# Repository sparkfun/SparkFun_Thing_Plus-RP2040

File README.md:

SparkFun Thing Plus RP2040
========================================

[*SparkFun Thing Plus RP2040 (DEV-17745)*](https://www.sparkfun.com/products/17745)

The SparkFun Thing Plus - RP2040 is a low-cost, high performance board with flexible digital interfaces featuring the Raspberry Pi Foundation's RP2040 microcontroller. Besides the Thing Plus or *Feather* footprint (with 18 GPIO pins), the board also includes an SD card slot, 16MB (128Mbit) flash memory, a JST single cell battery connector (with a charging circuit and fuel gauge sensor), an addressable WS2812 RGB LED, JTAG PTH pins, four (4-40 screw) mounting holes, and our signature Qwiic connector.

The RP2040 is supported with both C/C++ and MicroPython cross-platform development environments, including easy access to runtime debugging. It has UF2 boot and floating-point routines baked into the chip. While the chip has a large amount of internal RAM, the board includes an additional 16MB of external QSPI flash memory to store program code.

Repository Contents
-------------------

* **/Documentation** - Data sheets, additional product information
* **/Hardware** - Eagle design files (.brd, .sch)

Documentation
--------------

* **[Hookup Guide](https://learn.sparkfun.com/tutorials/1527)** - Basic hookup guide for the Thing Plus RP2040
* **[Raspberry Pi RP2040 Datasheet](https://datasheets.raspberrypi.org/rp2040/rp2040_datasheet.pdf)** - Datasheet for the RP2040
* **[SparkFun Graphical Datasheets](https://github.com/sparkfun/Graphical_Datasheets)** - Graphical datasheets for various SparkFun products.

Product Versions
----------------
* [DEV-17745](https://www.sparkfun.com/products/17745) -  initial release

License Information
-------------------

This product is _**open source**_! 

Please review the LICENSE.md file for license information. 

If you have any questions or concerns on licensing, please contact technical support on our [SparkFun forums](https://forum.sparkfun.com/viewforum.php?f=152).

Distributed as-is; no warranty is given.

- Your friends at SparkFun.

_<COLLABORATION CREDIT>_

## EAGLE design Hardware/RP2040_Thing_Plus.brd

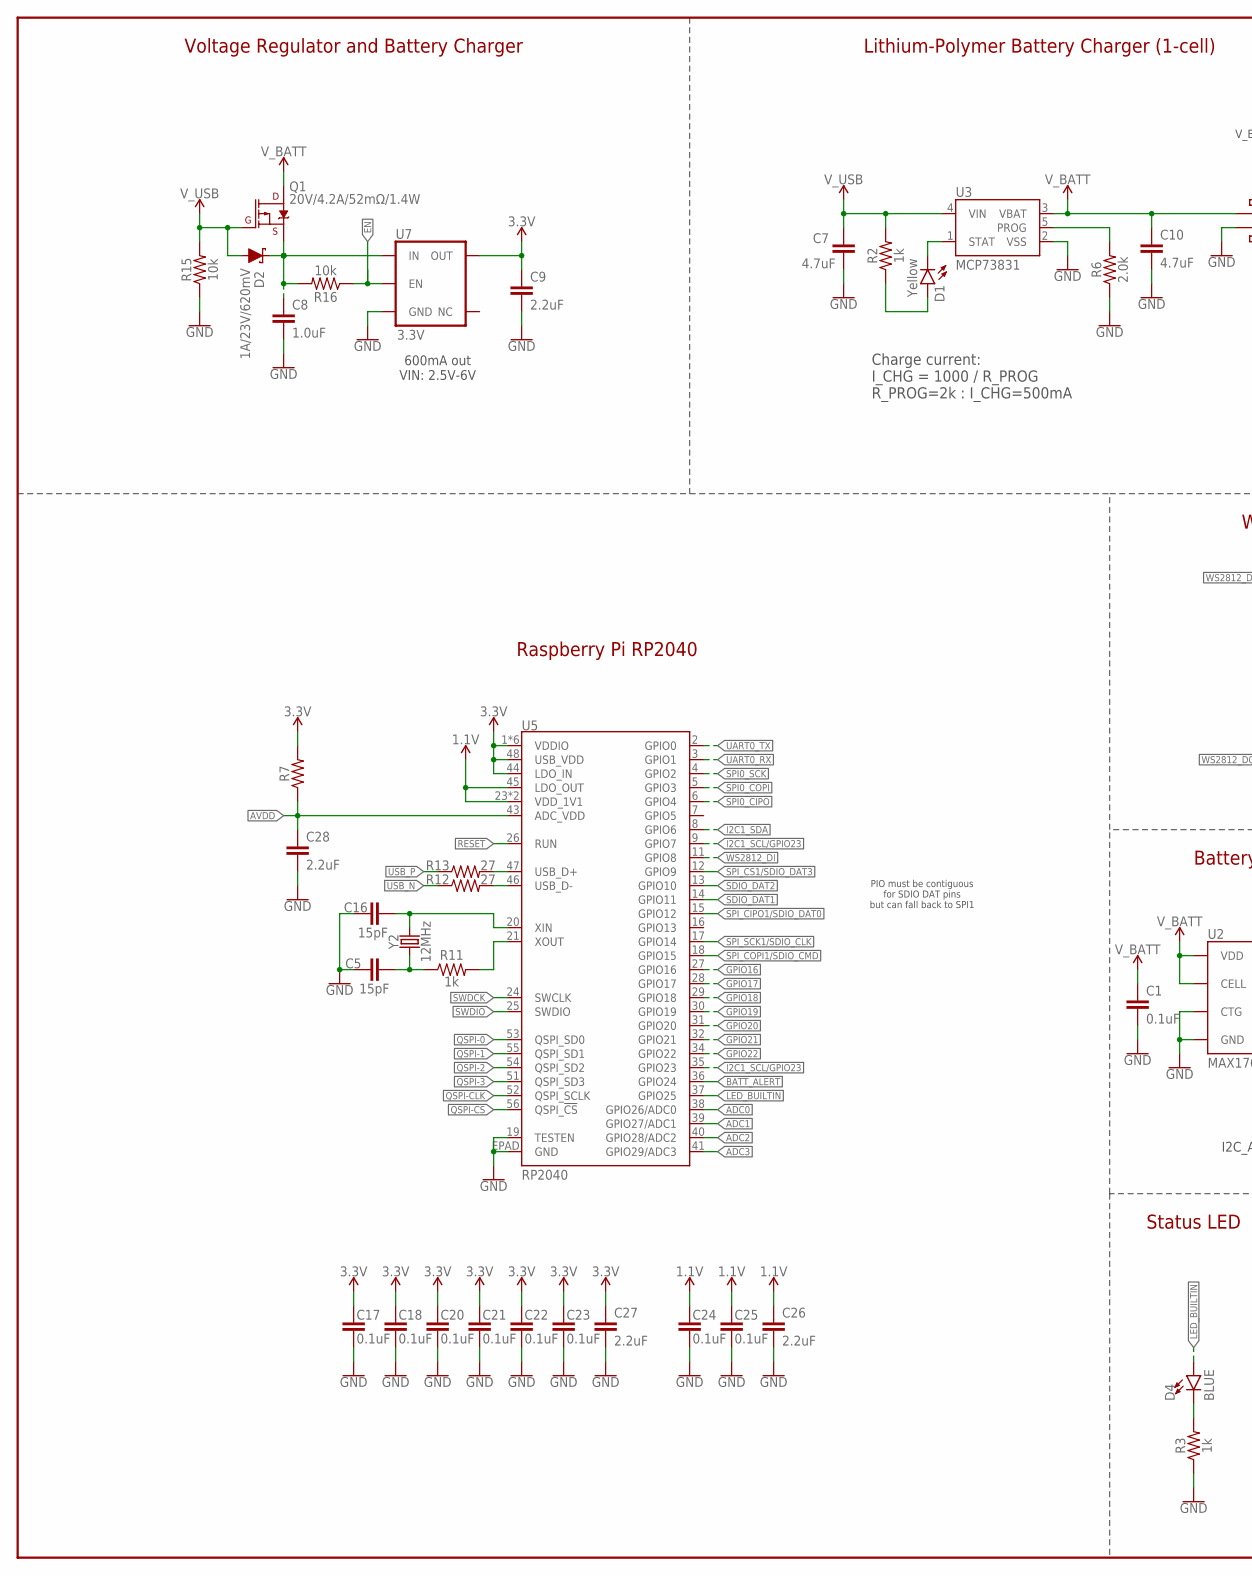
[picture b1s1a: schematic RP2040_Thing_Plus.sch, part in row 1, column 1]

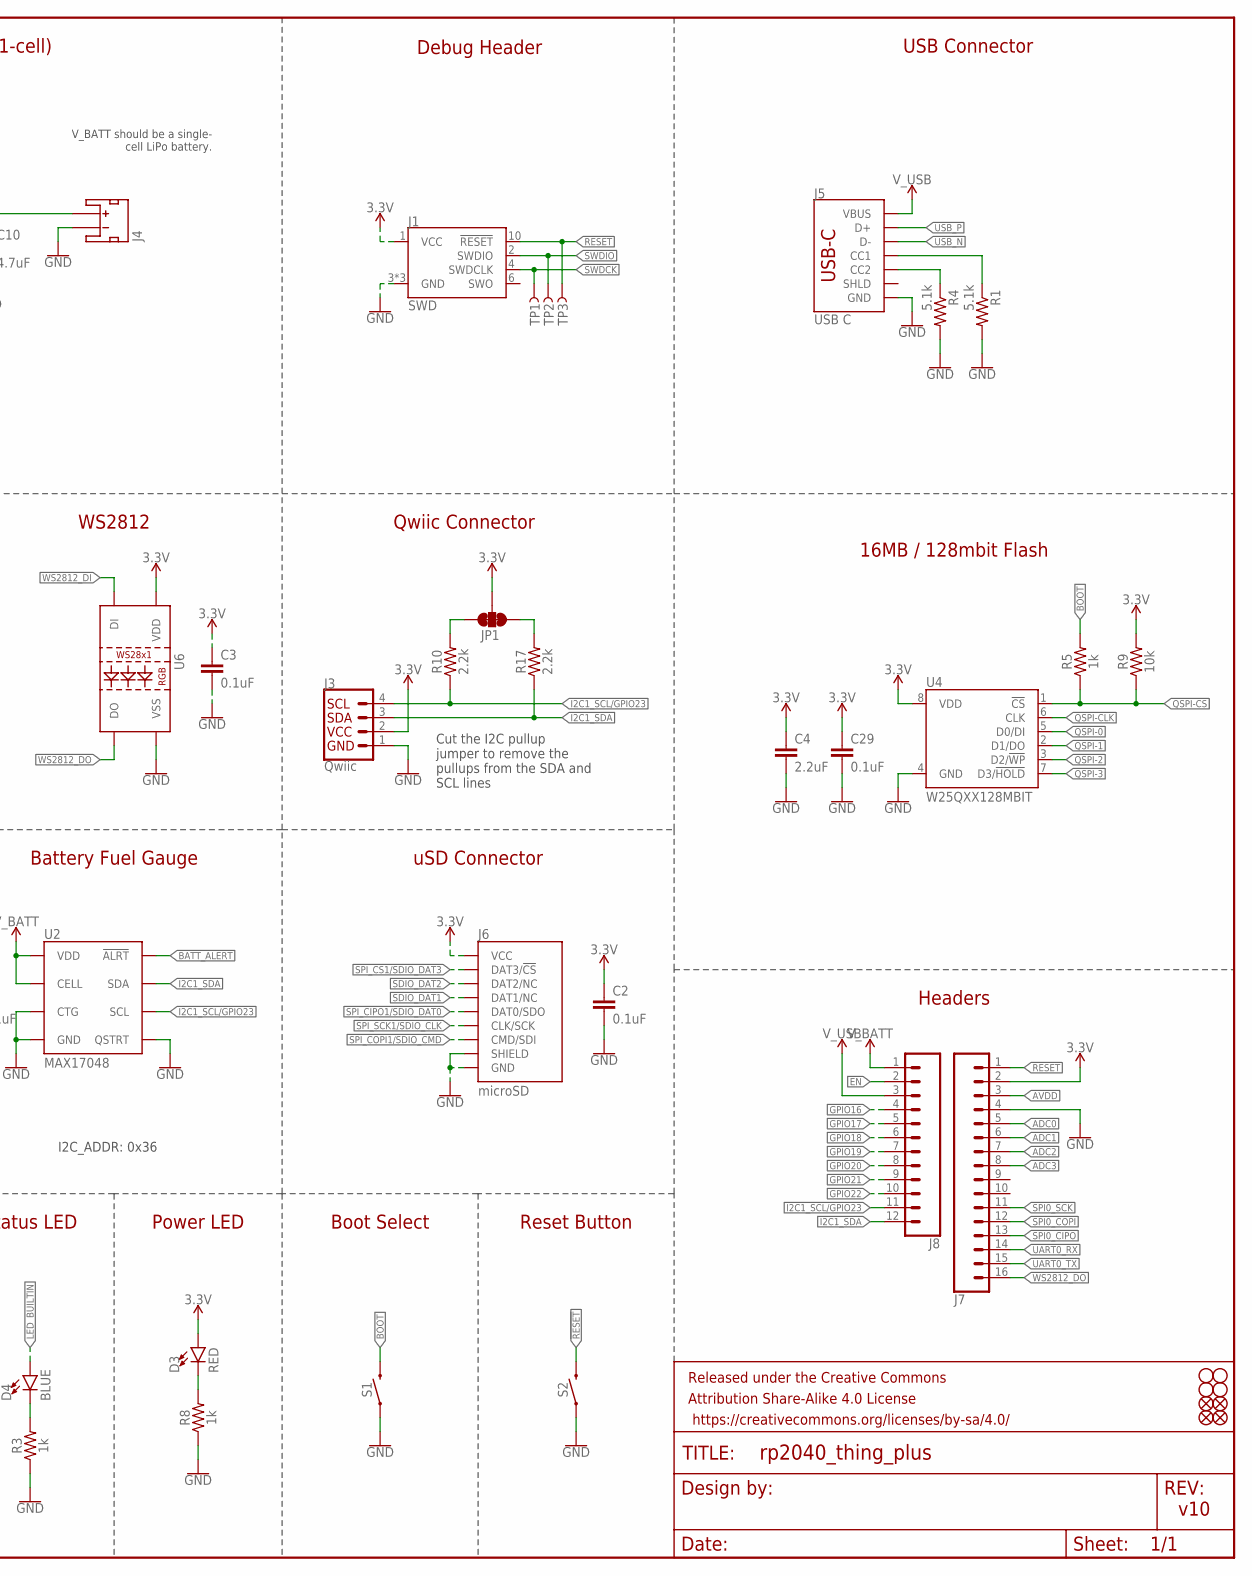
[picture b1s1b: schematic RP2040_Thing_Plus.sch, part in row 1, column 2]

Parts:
C1, C2, C3, C17, C18, C20, C21, C22, C23, C24, C25, C29: 0.1uF; 0402-TIGHT
C4, C9, C26, C27, C28: 2.2uF; 0402-TIGHT
C5, C16: 15pF; 0402-TIGHT
C7, C10: 4.7uF; 0402-TIGHT
C8: 1.0uF; 0402-TIGHT
D1: Yellow; LED-0603
D2: 1A/23V/620mV; SOD-323
D3: RED; LED-0603
D4: BLUE; LED-0603
FD1, FD2, FD3, FD4: FIDUCIALUFIDUCIAL; FIDUCIAL-MICRO
FRAME1: FRAME-LEDGER; CREATIVE_COMMONS
H1, H2, H3, H4: STAND-OFF
J1: SWD; 2X5-PTH-1.27MM
J3: Qwiic; JST04_1MM_RA
J4: JST_2MM_MALE; JST-2-SMD
J5: USB C; USB-C-16P-4LAYER-ISOLATED
J6: microSD; MICRO-SD-SOCKET
J7: CONN_161X16_NO_SILK; 1X16_NO_SILK
J8: CONN_12NO_SILK; 1X12_NO_SILK
JP1: JUMPER-SMT_3_2-NC_TRACE_SILK; SMT-JUMPER_3_2-NC_TRACE_SILK
Q1: 20V/4.2A/52mΩ/1.4W; SOT23-3
R1, R4: 5.1k; 0402-TIGHT
R2, R3, R5, R8, R11: 1k; 0402-TIGHT
R6: 2.0k; 0603
R7: 200OHM-0402T-1/16W-1%; 0402-TIGHT
R9, R15, R16: 10k; 0402-TIGHT
R10, R17: 2.2k; 0402-TIGHT
R12, R13: 27; 0402-TIGHT
S1, S2: MOMENTARY-SWITCH-SPST-SMD-5.2MM-TALL; TACTILE_SWITCH_SMD_5.2MM
TP1, TP2, TP3: TEST-POINT3X4; PAD.03X.04
U2: MAX17048; DFN-8
U3: MCP73831; SOT23-5
U4: W25QXX128MBIT; WSON-8-6X5-SKINNY_CENTERPAD
U5: RP2040; QFN-56
U6: WS2812-2020
U7: 3.3V; SOT23-5
Y2: 12MHz; CRYSTAL-SMD-2X2.5MM

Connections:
1.1V: C24.1, C25.1, C26.1, U5.23 (VDD_1V1), U5.45 (LDO_OUT), U5.50 (VDD_1V1)
3.3V: C2.1, C3.1, C4.1, C9.1, C17.1, C18.1, C20.1, C21.1, C22.1, C23.1, C27.1, C29.1, D3.A, J1.1 (VCC), J3.2, J6.VCC, J7.2, JP1.2, R7.2, R9.2, U4.8 (VDD), U5.1 (VDDIO), U5.10 (VDDIO), U5.22 (VDDIO), U5.33 (VDDIO), U5.42 (VDDIO), U5.44 (LDO_IN), U5.48 (USB_VDD), U5.49 (VDDIO), U6.4 (VDD), U7.5 (OUT)
!RESET!: J1.10 (!RESET), J7.1, S2.3 (2), TP3.P$1, U5.26 (RUN)
ADC0: J7.5, U5.38 (GPIO26/ADC0)
ADC1: J7.6, U5.39 (GPIO27/ADC1)
ADC2: J7.7, U5.40 (GPIO28/ADC2)
ADC3: J7.8, U5.41 (GPIO29/ADC3)
AVDD: C28.1, J7.3, R7.1, U5.43 (ADC_VDD)
BATT_ALERT: U2.5 (!ALRT), U5.36 (GPIO24)
BOOT: R5.2, S1.3 (2)
EN: J8.2, R16.1, U7.3 (EN)
GND: C1.2, C2.2, C3.2, C4.2, C5.1, C7.2, C8.2, C9.2, C10.2, C16.1, C17.2, C18.2, C20.2, C21.2, C22.2, C23.2, C24.2, C25.2, C26.2, C27.2, C28.2, C29.2, J1.3 (GND), J1.5 (GND), J1.9 (GND), J3.1, J4.1 (-), J5.GND, J5.GND2 (GND), J6.CD1 (SHIELD), J6.GND, J6.GND1 (GND), J6.GND3 (GND), J7.4, R1.2, R3.1, R4.2, R6.1, R8.1, R15.1, S1.1, S2.1, U2.1 (CTG), U2.4 (GND), U2.6 (QSTRT), U2.9 (GND), U3.2 (VSS), U4.4 (GND), U5.19 (TESTEN), U5.EPAD (GND), U6.2 (VSS), U7.2 (GND)
GPIO16: J8.4, U5.27 (GPIO16)
GPIO17: J8.5, U5.28 (GPIO17)
GPIO18: J8.6, U5.29 (GPIO18)
GPIO19: J8.7, U5.30 (GPIO19)
GPIO20: J8.8, U5.31 (GPIO20)
GPIO21: J8.9, U5.32 (GPIO21)
GPIO22: J8.10, U5.34 (GPIO22)
I2C1_SCL/GPIO23: J3.4, J8.11, R10.1, U2.7 (SCL), U5.9 (GPIO7), U5.35 (GPIO23)
I2C1_SDA: J3.3, J8.12, R17.1, U2.8 (SDA), U5.8 (GPIO6)
LED_BUILTIN: D4.A, U5.37 (GPIO25)
unnamed: D4.C, R3.2
unnamed: JP1.3, R10.2
unnamed: JP1.1, R17.2
unnamed: R11.2, U5.21 (XOUT)
unnamed: C16.2, U5.20 (XIN), Y2.P3 (2)
unnamed: C5.2, R11.1, Y2.P1 (1)
unnamed: D3.C, R8.2
unnamed: D1.C, U3.1 (STAT)
unnamed: J5.A5 (CC1), R1.1
unnamed: J5.B5 (CC2), R4.1
unnamed: R6.2, U3.5 (PROG)
unnamed: C8.1, D2.C, Q1.2 (S), R16.2, U7.1 (IN)
unnamed: D1.A, R2.1
QSPI-0: U4.5 (D0/DI), U5.53 (QSPI_SD0)
QSPI-1: U4.2 (D1/DO), U5.55 (QSPI_SD1)
QSPI-2: U4.3 (D2/!WP!), U5.54 (QSPI_SD2)
QSPI-3: U4.7 (D3/!HOLD!), U5.51 (QSPI_SD3)
QSPI-CLK: U4.6 (CLK), U5.52 (QSPI_SCLK)
QSPI-CS: R5.1, R9.1, U4.1 (!CS!), U5.56 (QSPI_!CS!)
SDIO_DAT1: J6.DAT1 (DAT1/NC), U5.14 (GPIO11)
SDIO_DAT2: J6.DAT2 (DAT2/NC), U5.13 (GPIO10)
SPI0_CIPO: J7.13, U5.6 (GPIO4)
SPI0_COPI: J7.12, U5.5 (GPIO3)
SPI0_SCK: J7.11, U5.4 (GPIO2)
SPI_!CS1!/SDIO_DAT3: J6.CS/DAT3 (DAT3/!CS!), U5.12 (GPIO9)
SPI_CIPO1/SDIO_DAT0: J6.DO/DAT0 (DAT0/SDO), U5.15 (GPIO12)
SPI_COPI1/SDIO_CMD: J6.DI/CMD (CMD/SDI), U5.18 (GPIO15)
SPI_SCK1/SDIO_CLK: J6.SCLK (CLK/SCK), U5.17 (GPIO14)
SWDCK: J1.4 (SWDCLK), TP1.P$1, U5.24 (SWCLK)
SWDIO: J1.2 (SWDIO), TP2.P$1, U5.25 (SWDIO)
UART0_RX: J7.14, U5.3 (GPIO1)
UART0_TX: J7.15, U5.2 (GPIO0)
USB_F_N: R12.2, U5.46 (USB_D-)
USB_F_P: R13.2, U5.47 (USB_D+)
USB_N: J5.A7 (D-), J5.B7 (D-), R12.1
USB_P: J5.A6 (D+), J5.B6 (D+), R13.1
V_BATT: C1.1, C10.1, J4.2 (+), J8.1, Q1.3 (D), U2.2 (CELL), U2.3 (VDD), U3.3 (VBAT)
V_USB: C7.1, D2.A, J5.VBUS1 (VBUS), J5.VBUS2 (VBUS), J8.3, Q1.1 (G), R2.2, R15.2, U3.4 (VIN)
WS2812_DI: U5.11 (GPIO8), U6.3 (DI)
WS2812_DO: J7.16, U6.1 (DO)

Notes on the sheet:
V_BATT should be a single- cell LiPo battery.
Charge current: I_CHG = 1000 / R_PROG R_PROG=2k : I_CHG=500mA
Voltage Regulator and Battery Charger
Lithium-Polymer Battery Charger (1-cell)
600mA out VIN: 2.5V-6V
Reset Button
Status LED
Headers
v10
Qwiic Connector
USB Connector
Cut the I2C pullup jumper to remove the pullups from the SDA and SCL lines
Raspberry Pi RP2040
PIO must be contiguous for SDIO DAT pins but can fall back to SPI1
16MB / 128mbit Flash
uSD Connector
Battery Fuel Gauge
WS2812
I2C_ADDR: 0x36
Boot Select
Debug Header
Power LED

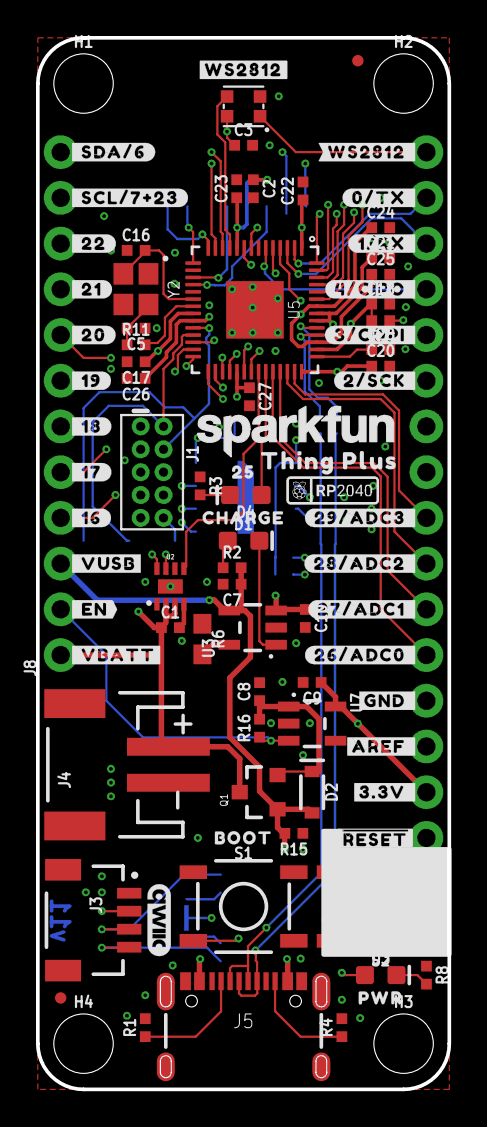
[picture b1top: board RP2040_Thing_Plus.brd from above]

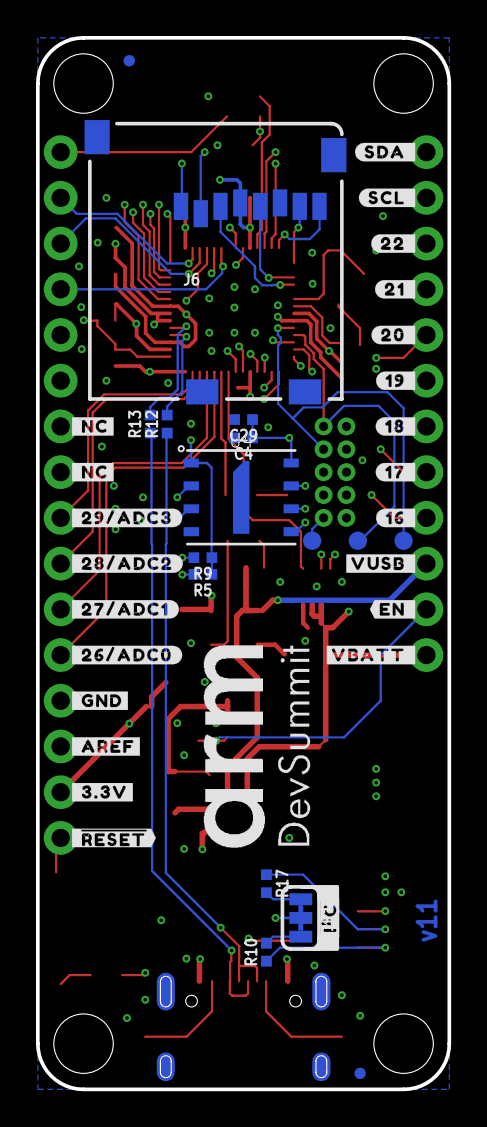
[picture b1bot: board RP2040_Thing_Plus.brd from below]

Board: 4 copper layers, 22.9 x 58.4 mm, 132 parts (40 on the bottom side), 62 nets.

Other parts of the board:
U$1: #_16#0
U$2: #_17#0
U$3: #_18#0
U$4: #_19#0
U$5: #_20#0
U$6: #_21#0
U$7: #_22#0
U$8: #_SCL#7#23#0
U$9: #_SDA#6#0
U$10: #WS2812_#0
U$11: #0#TX_#0
U$12: #1#RX_#0
U$13: #4#CIPO_#0
U$14: #3#COPI_#0
U$15: #2#SCK_#0
U$16: PWR0
U$17: #I�C#0
U$18: #29#ADC3_#0
U$19: #28#ADC2_#0
U$20: #27#ADC1_#0
U$21: #26#ADC0_#0
U$22: #_VUSB#0
U$23: #_EN#0
U$24: #_VBATT#0
U$25: #GND_#0
U$26: #AREF_#0
U$27: #3#3V_#0
U$28: ##RESET##0
U$29: RP2040_10
U$30: ARM1848_DEVSUMMIT_2021_LOGOS_ST3_STACKED#BLACK#JPG
U$31: ORDERING_INSTRUCTIONS
U$33: #SCL_#0
U$34: #SDA_#0
U$35: #_#RESET##0
U$36: #_3#3V#0
U$37: #_AREF#0
U$38: #_GND#0
U$39: #_26#ADC0#0
U$40: #_27#ADC1#0
U$41: #_28#ADC2#0
U$42: #_29#ADC3#0
U$45: SFE_LOGO_NAME_.1
U$47: THING_PLUS_0
U$54: 250
U$55: CHARGE0
U$56: BOOT0
U$57: #22_#0
U$58: #21_#0
U$59: #20_#0
U$60: #WS2812#0
U$61: #19_#0
U$62: #18_#0
U$63: #17_#0
U$64: QWIIC_4MM
U$65: #16_#0
U$66: #VUSB_#0
U$67: #EN_#0
U$68: #VBATT_#0
U$69, U$70: #_NC#0

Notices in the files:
parts and their libraries:
SparkFun-Resistors: Licensing: Creative Commons ShareAlike 4.0 International - https://creativecommons.org/licenses/by-sa/4.0
SparkFun-Aesthetics: Released under the Creative Commons Attribution Share-Alike 4.0 License
SparkFun-Aesthetics: https://creativecommons.org/licenses/by-sa/4.0
